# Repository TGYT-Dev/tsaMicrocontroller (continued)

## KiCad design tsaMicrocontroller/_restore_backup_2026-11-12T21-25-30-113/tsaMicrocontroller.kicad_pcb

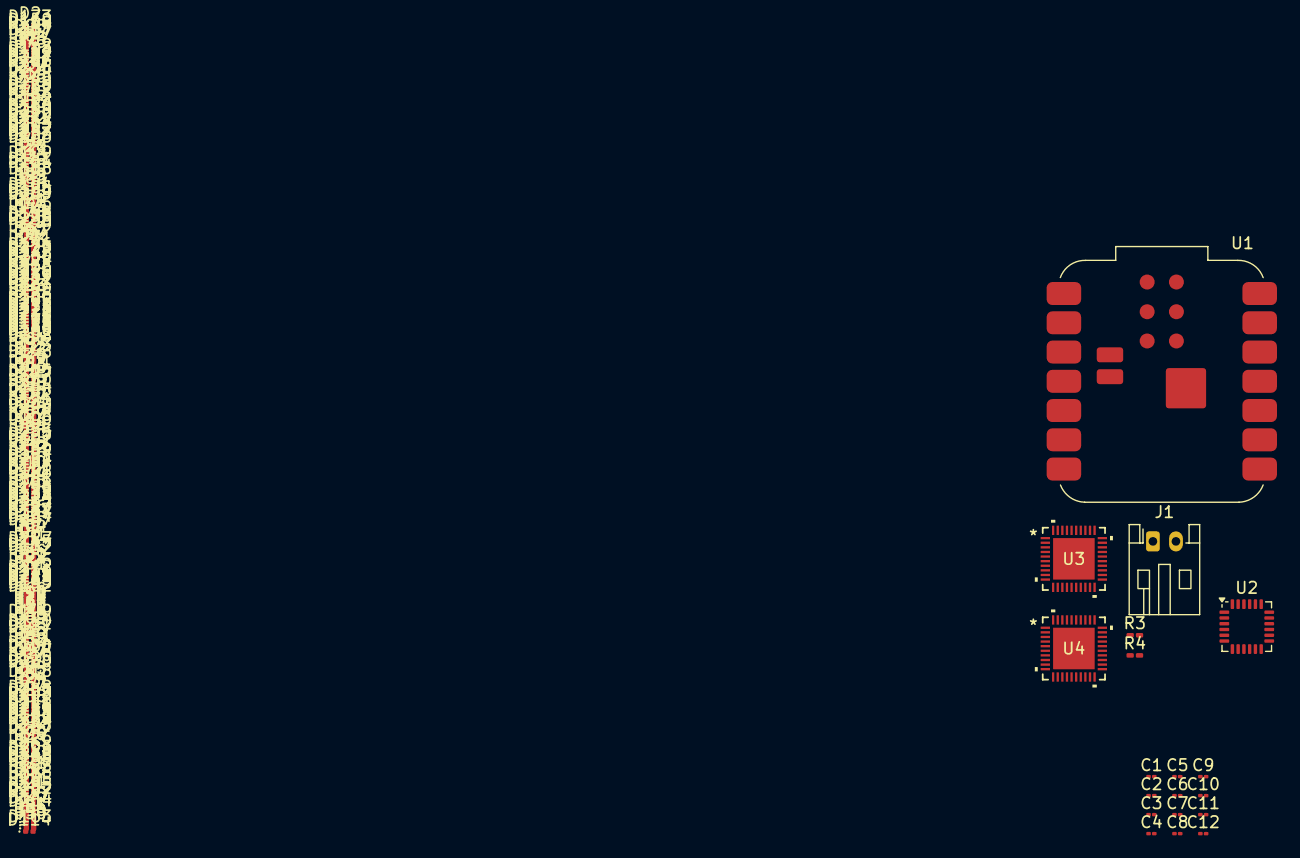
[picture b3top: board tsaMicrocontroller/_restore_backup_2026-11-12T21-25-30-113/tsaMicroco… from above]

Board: 2 copper layers, 275 parts (0 on the bottom side), 41 nets, no tracks yet.

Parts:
C1, C4: 0.1u; C_01005_0402Metric
C2: 2.2n; C_01005_0402Metric
C3: 10n; C_01005_0402Metric
C5, C6, C7, C8, C11, C12: 1u; C_01005_0402Metric
C9, C10: 1n; C_01005_0402Metric
D1, D2, D3, D4, D5, D6, D7, D8, D9, D10, D11, D12, D13, D14, D15, D16, D17, D18, D19, D20, D21, D22, D23, D24, D25, D26, D27, D28, D29, D30, D31, D32, D33, D34, D35, D36, D37, D38, D39, D40, D41, D42, D43, D44, D45, D46, D47, D48, D49, D50, D51, D52, D53, D54, D55, D56, D57, D58, D59, D60, D61, D62, D63, D64, D65, D66, D67, D68, D69, D70, D71, D72, D73, D74, D75, D76, D77, D78, D79, D80, D81, D82, D83, D84, D85, D86, D87, D88, D89, D90, D91, D92, D93, D94, D95, D96, D97, D98, D99, D100, D101, D102, D103, D104, D105, D106, D107, D108, D109, D110, D111, D112, D113, D114, D115, D116, D117, D118, D119, D120, D121, D122, D123, D124, D125, D126, D127, D128, D129, D130, D131, D132, D133, D134, D135, D136, D137, D138, D139, D140, D141, D142, D143, D144, D145, D146, D147, D148, D149, D150, D151, D152, D153, D154, D155, D156, D157, D158, D159, D160, D161, D162, D163, D164, D165, D166, D167, D168, D169, D170, D171, D172, D173, D174, D175, D176, D177, D178, D179, D180, D181, D182, D183, D184, D185, D186, D187, D188, D189, D190, D191, D192, D193, D194, D195, D196, D197, D198, D199, D200, D201, D202, D203, D204, D205, D206, D207, D208, D209, D210, D211, D212, D213, D214, D215, D216, D217, D218, D219, D220, D221, D222, D223, D224, D225, D226, D227, D228, D229, D230, D231, D232, D233, D234, D235, D236, D237, D238, D239, D240, D241, D242, D243, D244, D245, D246, D247, D248, D249, D250, D251, D252, D253, D254, D255, D256: LED; LED_0201_0603Metric
J1: Conn_01x02_Socket; JST_PH_S2B-PH-K_1x02_P2.00mm_Horizontal
R3, R4: 4.7k; R_0201_0603Metric_Pad0.64x0.40mm_HandSolder
U1: XIAO-ESP32-C3-SMD; MCU_Seeed_ESP32C3
U2: MPU-6050; InvenSense_QFN-24_4x4mm_P0.5mm
U3, U4: LP5868RKPR; VQFN40-RKP_TEX

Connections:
1: D1.2 (A), D2.2 (A), D3.2 (A), D4.2 (A), D5.2 (A), D6.2 (A), D7.2 (A), D8.2 (A), D9.2 (A), D10.2 (A), D11.2 (A), D12.2 (A), D13.2 (A), D14.2 (A), D15.2 (A), D16.2 (A), U3.10 (SW0)
2: D17.2 (A), D18.2 (A), D19.2 (A), D20.2 (A), D21.2 (A), D22.2 (A), D23.2 (A), D24.2 (A), D25.2 (A), D26.2 (A), D27.2 (A), D28.2 (A), D29.2 (A), D30.2 (A), D31.2 (A), D32.2 (A), U3.11 (SW1)
3: D33.2 (A), D34.2 (A), D35.2 (A), D36.2 (A), D37.2 (A), D38.2 (A), D39.2 (A), D40.2 (A), D41.2 (A), D42.2 (A), D43.2 (A), D44.2 (A), D45.2 (A), D46.2 (A), D47.2 (A), D48.2 (A), U3.12 (SW2)
4: D49.2 (A), D52.2 (A), D55.2 (A), D58.2 (A), D61.2 (A), D64.2 (A), D67.2 (A), D70.2 (A), D73.2 (A), D76.2 (A), D79.2 (A), D82.2 (A), D85.2 (A), D88.2 (A), D91.2 (A), D94.2 (A), U3.13 (SW3)
5: D50.2 (A), D53.2 (A), D56.2 (A), D59.2 (A), D62.2 (A), D65.2 (A), D68.2 (A), D71.2 (A), D74.2 (A), D77.2 (A), D80.2 (A), D83.2 (A), D86.2 (A), D89.2 (A), D92.2 (A), D95.2 (A), U3.14 (SW4)
6: D51.2 (A), D54.2 (A), D57.2 (A), D60.2 (A), D63.2 (A), D66.2 (A), D69.2 (A), D72.2 (A), D75.2 (A), D78.2 (A), D81.2 (A), D84.2 (A), D87.2 (A), D90.2 (A), D93.2 (A), D96.2 (A), U3.15 (SW5)
7: D97.2 (A), D99.2 (A), D101.2 (A), D103.2 (A), D105.2 (A), D107.2 (A), D109.2 (A), D111.2 (A), D113.2 (A), D115.2 (A), D117.2 (A), D119.2 (A), D121.2 (A), D123.2 (A), D125.2 (A), D127.2 (A), U3.17 (SW6)
8: D98.2 (A), D100.2 (A), D102.2 (A), D104.2 (A), D106.2 (A), D108.2 (A), D110.2 (A), D112.2 (A), D114.2 (A), D116.2 (A), D118.2 (A), D120.2 (A), D122.2 (A), D124.2 (A), D126.2 (A), D128.2 (A), U3.18 (SW7)
9: D129.2 (A), D133.2 (A), D137.2 (A), D141.2 (A), D145.2 (A), D149.2 (A), D153.2 (A), D157.2 (A), D161.2 (A), D165.2 (A), D169.2 (A), D173.2 (A), D177.2 (A), D181.2 (A), D185.2 (A), D189.2 (A), U4.10 (SW0)
10: D130.2 (A), D134.2 (A), D138.2 (A), D142.2 (A), D146.2 (A), D150.2 (A), D154.2 (A), D158.2 (A), D162.2 (A), D166.2 (A), D170.2 (A), D174.2 (A), D178.2 (A), D182.2 (A), D186.2 (A), D190.2 (A), U4.11 (SW1)
11: D131.2 (A), D135.2 (A), D139.2 (A), D143.2 (A), D147.2 (A), D151.2 (A), D155.2 (A), D159.2 (A), D163.2 (A), D167.2 (A), D171.2 (A), D175.2 (A), D179.2 (A), D183.2 (A), D187.2 (A), D191.2 (A), U4.12 (SW2)
12: D132.2 (A), D136.2 (A), D140.2 (A), D144.2 (A), D148.2 (A), D152.2 (A), D156.2 (A), D160.2 (A), D164.2 (A), D168.2 (A), D172.2 (A), D176.2 (A), D180.2 (A), D184.2 (A), D188.2 (A), D192.2 (A), U4.13 (SW3)
13: D193.2 (A), D197.2 (A), D201.2 (A), D205.2 (A), D209.2 (A), D213.2 (A), D217.2 (A), D221.2 (A), D225.2 (A), D229.2 (A), D233.2 (A), D237.2 (A), D241.2 (A), D245.2 (A), D249.2 (A), D253.2 (A), U4.14 (SW4)
14: D194.2 (A), D198.2 (A), D202.2 (A), D206.2 (A), D210.2 (A), D214.2 (A), D218.2 (A), D222.2 (A), D226.2 (A), D230.2 (A), D234.2 (A), D238.2 (A), D242.2 (A), D246.2 (A), D250.2 (A), D254.2 (A), U4.15 (SW5)
15: D195.2 (A), D199.2 (A), D203.2 (A), D207.2 (A), D211.2 (A), D215.2 (A), D219.2 (A), D223.2 (A), D227.2 (A), D231.2 (A), D235.2 (A), D239.2 (A), D243.2 (A), D247.2 (A), D251.2 (A), D255.2 (A), U4.17 (SW6)
16: D196.2 (A), D200.2 (A), D204.2 (A), D208.2 (A), D212.2 (A), D216.2 (A), D220.2 (A), D224.2 (A), D228.2 (A), D232.2 (A), D236.2 (A), D240.2 (A), D244.2 (A), D248.2 (A), D252.2 (A), D256.2 (A), U4.18 (SW7)
+3V3: C3.1, C4.2, C5.2, C6.2, C7.2, C8.2, C9.2, C10.2, R3.1, R4.1, U1.12 (3V3_OUT), U2.8 (VLOGIC), U2.13 (VDD), U3.16 (VLED), U3.39 (VIO_EN), U3.40 (VCC), U4.16 (VLED), U4.37 (ADDR0_MISO), U4.39 (VIO_EN), U4.40 (VCC)
+BATT: J1.2, U1.21 (VBAT)
A: D1.1 (K), D17.1 (K), D33.1 (K), D49.1 (K), D50.1 (K), D51.1 (K), D97.1 (K), D98.1 (K), D129.1 (K), D130.1 (K), D131.1 (K), D132.1 (K), D193.1 (K), D194.1 (K), D195.1 (K), D196.1 (K), U3.1 (CS0), U4.1 (CS0)
B: D2.1 (K), D18.1 (K), D34.1 (K), D52.1 (K), D53.1 (K), D54.1 (K), D99.1 (K), D100.1 (K), D133.1 (K), D134.1 (K), D135.1 (K), D136.1 (K), D197.1 (K), D198.1 (K), D199.1 (K), D200.1 (K), U3.2 (CS1), U4.2 (CS1)
C: D3.1 (K), D19.1 (K), D35.1 (K), D55.1 (K), D56.1 (K), D57.1 (K), D101.1 (K), D102.1 (K), D137.1 (K), D138.1 (K), D139.1 (K), D140.1 (K), D201.1 (K), D202.1 (K), D203.1 (K), D204.1 (K), U3.3 (CS2), U4.3 (CS2)
D: D4.1 (K), D20.1 (K), D36.1 (K), D58.1 (K), D59.1 (K), D60.1 (K), D103.1 (K), D104.1 (K), D141.1 (K), D142.1 (K), D143.1 (K), D144.1 (K), D205.1 (K), D206.1 (K), D207.1 (K), D208.1 (K), U3.4 (CS3), U4.4 (CS3)
E: D5.1 (K), D21.1 (K), D37.1 (K), D61.1 (K), D62.1 (K), D63.1 (K), D105.1 (K), D106.1 (K), D145.1 (K), D146.1 (K), D147.1 (K), D148.1 (K), D209.1 (K), D210.1 (K), D211.1 (K), D212.1 (K), U3.5 (CS4), U4.5 (CS4)
F: D6.1 (K), D22.1 (K), D38.1 (K), D64.1 (K), D65.1 (K), D66.1 (K), D107.1 (K), D108.1 (K), D149.1 (K), D150.1 (K), D151.1 (K), D152.1 (K), D213.1 (K), D214.1 (K), D215.1 (K), D216.1 (K), U3.6 (CS5), U4.6 (CS5)
G: D7.1 (K), D23.1 (K), D39.1 (K), D67.1 (K), D68.1 (K), D69.1 (K), D109.1 (K), D110.1 (K), D153.1 (K), D154.1 (K), D155.1 (K), D156.1 (K), D217.1 (K), D218.1 (K), D219.1 (K), D220.1 (K), U3.7 (CS6), U4.7 (CS6)
GND: C1.1, C2.1, C3.2, C4.1, C5.1, C6.1, C7.1, C8.1, C11.1, C12.1, J1.1, U1.13 (GND), U1.18 (GND), U1.22 (GND), U2.1 (CLKIN), U2.9 (AD0), U2.11 (FSYNC), U2.18 (GND), U3.31 (AGND), U3.33 (IFS), U3.34 (VSYNC), U3.37 (ADDR0_MISO), U3.38 (ADDR1_SS), U3.41 (EXPOSED_THERMAL_PAD), U4.31 (AGND), U4.33 (IFS), U4.34 (VSYNC), U4.38 (ADDR1_SS), U4.41 (EXPOSED_THERMAL_PAD)
H: D8.1 (K), D24.1 (K), D40.1 (K), D70.1 (K), D71.1 (K), D72.1 (K), D111.1 (K), D112.1 (K), D157.1 (K), D158.1 (K), D159.1 (K), D160.1 (K), D221.1 (K), D222.1 (K), D223.1 (K), D224.1 (K), U3.8 (CS7), U4.8 (CS7)
I: D9.1 (K), D25.1 (K), D41.1 (K), D73.1 (K), D74.1 (K), D75.1 (K), D113.1 (K), D114.1 (K), D161.1 (K), D162.1 (K), D163.1 (K), D164.1 (K), D225.1 (K), D226.1 (K), D227.1 (K), D228.1 (K), U3.9 (CS8), U4.9 (CS8)
J: D10.1 (K), D26.1 (K), D42.1 (K), D76.1 (K), D77.1 (K), D78.1 (K), D115.1 (K), D116.1 (K), D165.1 (K), D166.1 (K), D167.1 (K), D168.1 (K), D229.1 (K), D230.1 (K), D231.1 (K), D232.1 (K), U3.22 (CS9), U4.22 (CS9)
K: D11.1 (K), D27.1 (K), D43.1 (K), D79.1 (K), D80.1 (K), D81.1 (K), D117.1 (K), D118.1 (K), D169.1 (K), D170.1 (K), D171.1 (K), D172.1 (K), D233.1 (K), D234.1 (K), D235.1 (K), D236.1 (K), U3.23 (CS10), U4.23 (CS10)
L: D12.1 (K), D28.1 (K), D44.1 (K), D82.1 (K), D83.1 (K), D84.1 (K), D119.1 (K), D120.1 (K), D173.1 (K), D174.1 (K), D175.1 (K), D176.1 (K), D237.1 (K), D238.1 (K), D239.1 (K), D240.1 (K), U3.24 (CS11), U4.24 (CS11)
M: D13.1 (K), D29.1 (K), D45.1 (K), D85.1 (K), D86.1 (K), D87.1 (K), D121.1 (K), D122.1 (K), D177.1 (K), D178.1 (K), D179.1 (K), D180.1 (K), D241.1 (K), D242.1 (K), D243.1 (K), D244.1 (K), U3.25 (CS12), U4.25 (CS12)
N: D14.1 (K), D30.1 (K), D46.1 (K), D88.1 (K), D89.1 (K), D90.1 (K), D123.1 (K), D124.1 (K), D181.1 (K), D182.1 (K), D183.1 (K), D184.1 (K), D245.1 (K), D246.1 (K), D247.1 (K), D248.1 (K), U3.26 (CS13), U4.26 (CS13)
unnamed: C2.2, U2.20 (CPOUT)
unnamed: C1.2, U2.10 (REGOUT)
unnamed: C12.2, U3.32 (VCAP)
unnamed: C11.2, U4.32 (VCAP)
O: D15.1 (K), D31.1 (K), D47.1 (K), D91.1 (K), D92.1 (K), D93.1 (K), D125.1 (K), D126.1 (K), D185.1 (K), D186.1 (K), D187.1 (K), D188.1 (K), D249.1 (K), D250.1 (K), D251.1 (K), D252.1 (K), U3.27 (CS14), U4.27 (CS14)
P: D16.1 (K), D32.1 (K), D48.1 (K), D94.1 (K), D95.1 (K), D96.1 (K), D127.1 (K), D128.1 (K), D189.1 (K), D190.1 (K), D191.1 (K), D192.1 (K), D253.1 (K), D254.1 (K), D255.1 (K), D256.1 (K), U3.28 (CS15), U4.28 (CS15)
SCL: R4.2, U1.6 (D5), U2.23 (SCL), U3.35 (SCL_SCLK), U4.35 (SCL_SCLK)
SDA: R3.2, U1.5 (D4), U2.24 (SDA), U3.36 (SDA_MOSI), U4.36 (SDA_MOSI)
